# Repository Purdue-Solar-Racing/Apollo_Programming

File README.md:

# Apollo_Programming
Purdue Solar main code repository for the Apollo car. 

## Subsystem Hardware Status
Status Key and Due Dates
0. Not Started
1. Started in Research
2. In Schematic Work
3. Schematic Finished - Oct 23rd, 2021
4. PCB Layout Finished - Nov 13/20th, 2021
5. Manufactuing Stage
6. Debugged and Working

| Subsystem                 | Lead                | Status | Members                   | Notes |
|---------------------------|---------------------|--------|---------------------------|-------|
| Battery Protection System | Nate Nauman         | 2/3    | Nicholas Gildenhuys       |       |
| Driver Display            | Rachael Getz        | 1      | Darin Tsai, Jing Hoon     |       |
| Light Controller          | Darin Tsai          | 3      |                           |       |
| Junction Controller       | Nicholas Gildenhuys | 0      |                           |       |
| Motor Controller          | Nate Nauman         | 2      | Nicholas Gildenhuys       |       |
| Solar Array Controller    | Landon Lindsay      | 3      | Dhanu De Silva, Jing Hoon |       |
| Vehicle Controller        | Roshni Sharma       | 2/3    |                           |       |
| Wheel Controller          | Nicholas Gildenhuys | 3      |                           |       |

## Subsystem Software Status
Status Key:
0. Not Started
1. Started in Research
2. Prelim Code
3. Main Functions Built Out
4. Integration Stage
5. Integration Finished

| Subsystem                 | Lead                | Status | Members                    | Notes |
|---------------------------|---------------------|--------|----------------------------|-------|
| Battery Protection System |                     | 0      | 			                      |       |
| Driver Display            | 			              | 0      |                            |       |
| Light Controller          | 		                | 0      |                            |       |
| Junction Controller       | 			              | 0      |                            |       |
| Motor Controller          | 		                | 0      | 			                      |       |
| Solar Array Controller    | 		                | 0      | 			                      |       |
| Vehicle Controller        | 		                | 0      |                            |       |
| Wheel Controller          | 			              | 0      |                            |       |

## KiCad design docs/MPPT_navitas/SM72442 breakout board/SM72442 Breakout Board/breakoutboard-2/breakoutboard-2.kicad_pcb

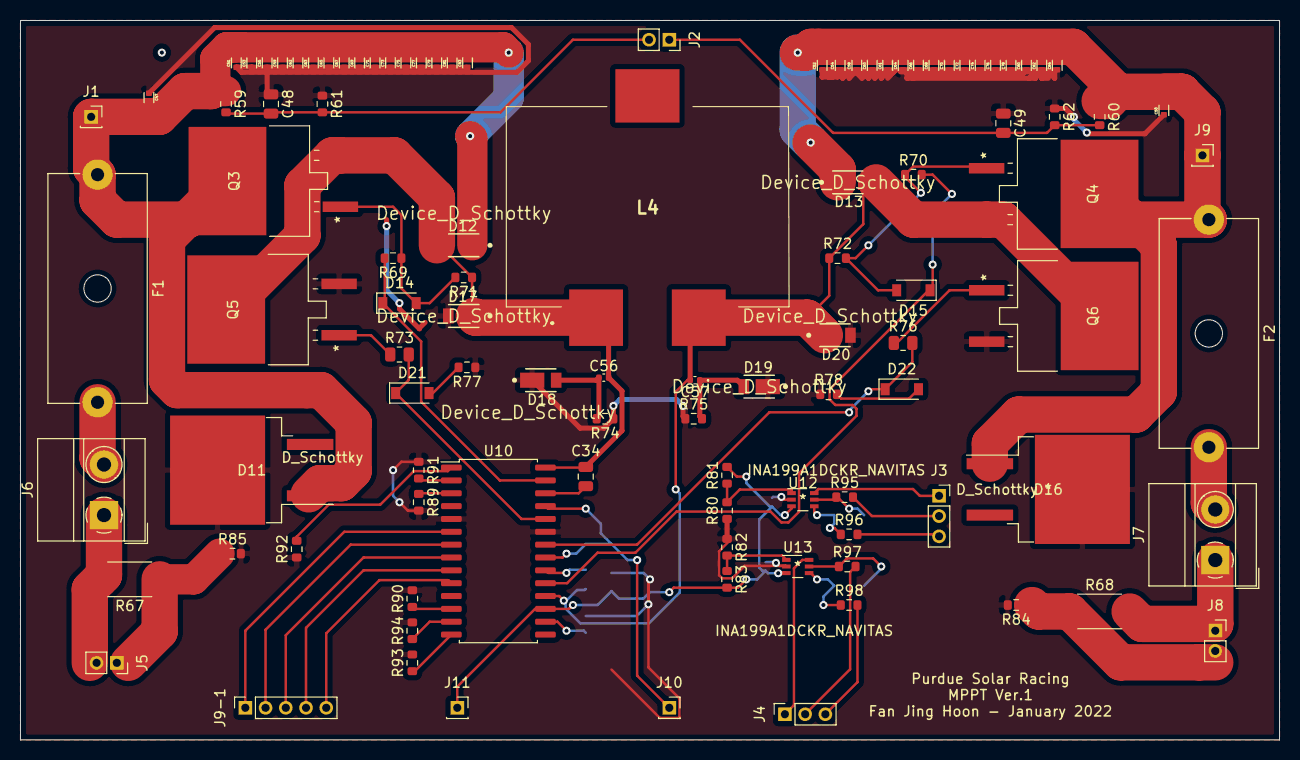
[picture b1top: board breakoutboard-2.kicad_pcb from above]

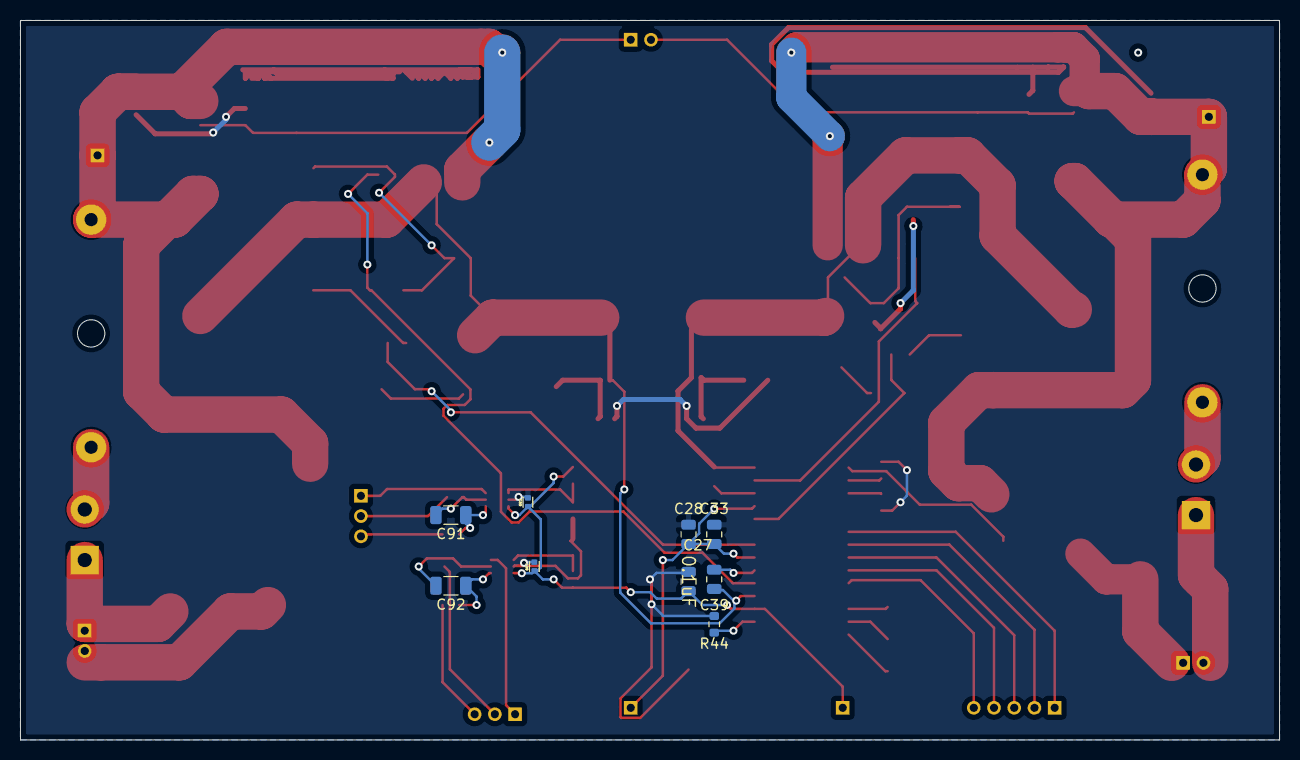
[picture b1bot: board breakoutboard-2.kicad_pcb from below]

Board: 2 copper layers, 124.5 x 71.1 mm, 114 parts (9 on the bottom side), 53 nets.

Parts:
C27: 0.1uF; C_0805_2012Metric
C28, C33: 1uF; C_0805_2012Metric
C34, C39: 0.47uF; C_0805_2012Metric
C47, C50, C51, C52, C53, C54, C55, C58, C59, C60, C61, C62, C63, C64, C65, C66, C67, C68, C69, C70, C71, C72, C73, C74, C75, C76, C77, C78, C79, C80, C81, C82, C83, C84: 2.2uF; CAPC1005X55N
C48, C49: .01uF; C_0805_2012Metric
C56, C57: 470pF; C_0402_1005Metric
C89, C99: .1uF; CAPC1005X55N
C91, C92: 10uF; C_1206_3216Metric
D11, D16: D_Schottky; TO-263-2
D12, D13, D17, D18, D19, D20: Device_D_Schottky; Diodes_Inc.-PowerDI123-03_2017-0-MFG
D14: Device_D_Schottky; D_SOD-123
D15, D21, D22: D_Schottky; D_SOD-123
F1, F2: 10A; Fuseholder_Cylinder-5x20mm_Schurter_0031_8201_Horizontal_Op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
J1: PV_IN; PinSocket_1x01_P2.00mm_Vertical
J2: Connector_Generic_Conn_01x02; PinSocket_1x02_P2.00mm_Vertical
J3: Iin_sense_INA; PinSocket_1x03_P2.00mm_Vertical
J4: Iout_sense_INA; PinSocket_1x03_P2.00mm_Vertical
J5: Iin_sense; PinSocket_1x02_P2.00mm_Vertical
J6: PV; TerminalBlock_MetzConnect_Type011_RT05502HBWC_1x02_P5.00mm_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
J7: BAT; TerminalBlock_MetzConnect_Type011_RT05502HBWC_1x02_P5.00mm_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
J8: Iout_sense; PinSocket_1x02_P2.00mm_Vertical
J9: Vout; PinSocket_1x01_P2.00mm_Vertical
J9-1: Connector_Generic_Conn_01x05; PinSocket_1x05_P2.00mm_Vertical
J10: 10V; PinSocket_1x01_P2.00mm_Vertical
J11: 5V_conn; PinSocket_1x01_P2.00mm_Vertical
L4: L_Core_Iron; SER2915L682KL
Q3, Q4, Q5, Q6: 2N7002; IRF8010STRLPBF
R44, R71, R72, R77, R78, R80, R82: 10k; R_0603_1608Metric
R59, R60: 26.1k; R_0603_1608Metric
R61, R62: 2k; R_0603_1608Metric
R67, R68: .004; R_2512_6332Metric
R69, R70, R74, R75, R95, R96, R97, R98: 10; R_0603_1608Metric
R73, R76: 4.99; R_0805_2012Metric
R81, R83: DNP; R_0603_1608Metric
R84, R85: short; R_0603_1608Metric
R89, R90, R91, R92, R93, R94: 0; R_0603_1608Metric
U10: Driver_FET_SM72295MA_Navitas; SOIC-28W_7.5x17.9mm_P1.27mm
U12, U13: INA199A1DCKR_NAVITAS; INA214CIDCKR

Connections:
+5V: C27.2, C89.1, C99.1, J11.1, R81.2, R83.2, U10.17, U12.3, U13.3
GND: C27.1, C28.2, C33.2, C47.1, C48.1, C49.1, C50.1, C51.1, C52.1, C53.1, C54.1, C55.1, C58.1, C59.1, C60.1, C61.1, C62.1, C63.1, C64.1, C65.1, C66.1, C67.1, C68.1, C69.1, C70.1, C71.1, C72.1, C73.1, C74.1, C75.1, C76.1, C77.1, C78.1, C79.1, C80.1, C81.1, C82.1, C83.1, C84.1, C89.2, C99.2, D11.2, D16.2, D17.2, D18.1, D19.1, D20.2, Q5.2, Q6.2, R44.1, R61.1, R62.1, R74.1, R75.1, R77.1, R78.1, R80.1, R82.1, R84.2, R85.2, R89.2, R90.2, R91.1, R92.1, R93.2, R94.2, U10.5, U10.23, U12.2, U13.2
HOA: D14.1, R69.2, U10.27
HOB: D15.1, R70.2, U10.19
HSA: C34.1, C56.2, D12.2, D17.1, L4.1, Q3.2, Q5.3, R71.1, U10.28
HSB: C39.1, C57.2, D13.2, D20.1, L4.2, Q4.2, Q6.3, R72.1, U10.18
Iin_Sense+: J5.1, R67.1, R85.1
Iin_Sense-: J5.2, J6.1, R67.2
Iout_Sense+: J7.1, J8.1, R68.2
Iout_Sense-: J8.2, R68.1, R84.1
LOA: D21.1, R73.2, U10.24
LOB: D22.1, R76.2, U10.22
unnamed: C28.1, C33.1, J10.1, U10.21, U10.25
unnamed: C34.2, U10.26
unnamed: C39.2, U10.20
unnamed: C47.2, C51.2, C53.2, C55.2, C59.2, C62.2, C63.2, C65.2, C67.2, C69.2, C71.2, C73.2, C75.2, C77.2, C79.2, C81.2, C83.2, D11.1, D12.1, F1.1, J1.1, Q3.3, R59.1
unnamed: C50.2, C52.2, C54.2, C58.2, C60.2, C61.2, C64.2, C66.2, C68.2, C70.2, C72.2, C74.2, C76.2, C78.2, C80.2, C82.2, C84.2, D13.1, D16.1, F2.1, J9.1, Q4.3, R60.1
unnamed: C56.1, D18.2, R74.2
unnamed: C57.1, D19.2, R75.2
unnamed: C91.1, R96.1, U12.4
unnamed: C91.2, R95.1, U12.5
unnamed: C92.1, R98.1, U13.4
unnamed: C92.2, R97.1, U13.5
unnamed: D14.2, Q3.1, R69.1, R71.2
unnamed: D15.2, Q4.1, R70.1, R72.2
unnamed: D21.2, R77.2
unnamed: D22.2, R78.2
unnamed: F1.2, J6.2
unnamed: F2.2, J7.2
unnamed: J3.1, U12.6
unnamed: J3.2, R95.2
unnamed: J3.3, R96.2
unnamed: J4.1, U13.6
unnamed: J4.2, R97.2
unnamed: J4.3, R98.2
unnamed: J9-1.1, U10.6
unnamed: J9-1.2, U10.7
unnamed: J9-1.3, U10.8
unnamed: J9-1.4, U10.9
unnamed: J9-1.5, U10.10
unnamed: Q5.1, R73.1
unnamed: Q6.1, R76.1
unnamed: R44.2, U10.16
unnamed: R80.2, R81.1, U12.1
unnamed: R82.2, R83.1, U13.1
unnamed: R89.1, U10.3
unnamed: R90.1, U10.12
unnamed: R91.2, U10.2
unnamed: R92.2, U10.1
unnamed: R93.1, U10.14
unnamed: R94.1, U10.13
Vin_Sense: C48.2, J2.2, R59.2, R61.2
Vout_Sense: C49.2, J2.1, R60.2, R62.2

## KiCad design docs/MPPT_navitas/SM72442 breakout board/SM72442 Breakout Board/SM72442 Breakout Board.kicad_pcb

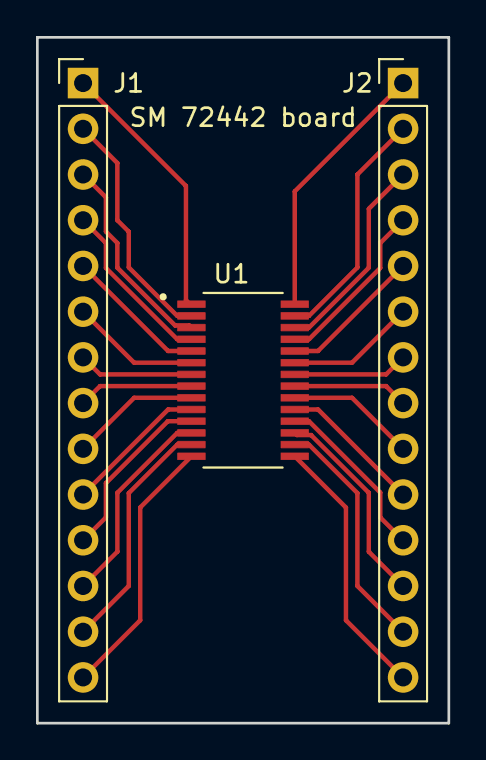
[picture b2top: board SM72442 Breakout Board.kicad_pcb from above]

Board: 2 copper layers, 22.9 x 38.1 mm, 3 parts (0 on the bottom side), 28 nets.

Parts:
J1, J2: Conn_01x14_Male; PinHeader_1x14_P2.54mm_Vertical
U1: SM72442MT_NOPB; SOP65P640X120-28N

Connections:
/*RST: J1.1, U1.1
/A0: J1.14, U1.14
/A2: J2.13, U1.16
/A4: J2.11, U1.18
/A6: J2.9, U1.20
/AIIN: J2.10, U1.19
/AIOUT: J2.8, U1.21
/AVIN: J2.14, U1.15
/AVOUT: J2.12, U1.17
/HIA: J2.3, U1.26
/HIB: J2.4, U1.25
/I2C0: J1.6, U1.6
/I2C1: J1.7, U1.7
/I2C2: J2.7, U1.22
/LIA: J2.2, U1.27
/LIB: J2.5, U1.24
/NC1: J1.2, U1.2
/NC2: J1.5, U1.5
/NC3: J1.10, U1.10
/NC4: J2.6, U1.23
/PM: J2.1, U1.28
/PM_OUT: J1.11, U1.11
/SCL: J1.8, U1.8
/SDA: J1.9, U1.9
/VDDA: J1.12, U1.12
/VDDD: J1.3, U1.3
/VSSA: J1.13, U1.13
/VSSD: J1.4, U1.4

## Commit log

2021-01-30 Initial documentation of the subsystems
2021-01-30 Edited gitignore to include latex log files
2021-01-30 Preliminary source files for can init and rough outline for light control
2021-01-30 Init some button code
2021-02-07 Setup the eclipse project stuff
2021-02-27 test commit
2021-02-27 Test commit 2
2021-02-27 Test comment #3
2021-02-27 clear comments
2021-03-06 CAN Manual
2021-03-06 added Pseudocode
2021-03-06 changes to bxcan
2021-03-06 Most of Rick's board CADed up
2021-03-13 finish P and O pseudocode
2021-03-20 Initial Wheel controller finished, just need exact values and proper power routing
2021-03-20 Initial commit for subsystem schematics
2021-04-10 added lcd driver display info to schematic and symbol
2021-04-24 Additions to driver display, layed out all SPI signals.
2021-04-24 SPI prelim code examples from 362
2021-09-04 STM32 PDF Schematic Added
2021-09-04 updated gitignore
2021-09-04 updated gitignore hopefully works now
2021-09-04 updated gitignore hopefully works now maybe
2021-09-04 Updaed Readme
2021-09-05 The files are the replica of STM32 schematics with some concerns stated in the txt file
2021-09-11 Adding Empty subsystems documentation to the docs
2021-09-25 Uploaded my schematics (wip)
2021-10-13 Create Vehicular Controller Subsystem.sch
    Starting phase of the Vehicular Controller Subsystem schematic with base board and digital pot.
2021-10-16 MPPT schematics file upload
2021-10-16 Library for MPPT
2021-10-16 Update Vehicular Controller Subsystem.sch
    Placed Labels on pins that will need to be used for I2C.
    Added hierarchical pins on the base board sheet.
2021-10-16 Created power Electronics for mppt
2021-10-23 update to hierarchical connection
2021-10-23 update to hierarchical sheets location
2021-10-23 update on stm32
2021-10-23 Update STM32_MPPT.sch
    Test Push
2021-10-23 Renaming redundant parts
2021-10-23 updated stm32 in mppt
2021-10-23 Finished, need Calculations
2021-10-24 folder reordering
2021-10-26 fixed some problem
2021-10-29 Throttle System V1
2021-10-30 update on analog input pins
2021-10-30 update on connection
2021-11-06 Update on SM 72442 A0 resistance
2021-11-08 Adding exel file for the lighting system purchases
2021-11-11 Breakout board
2021-11-13 breakout board update
2021-11-13 lib update
2021-11-23 relabel + recalc
2021-11-23 update on PCB
2021-11-27 PCB update
2021-12-07 Lighting Parts Footprints
2022-01-03 update on pcb (in progress)
2022-01-06 PCB layout updated, next step to make traces & dimensions
2022-01-17 MPPT PCB completed, Gerber generated
2022-01-18 footprint fixed, Gerber updated
2022-03-10 update from some time ago

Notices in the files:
parts and their libraries:
Copyright 2021 Accelerated Designs. All rights reserved.
